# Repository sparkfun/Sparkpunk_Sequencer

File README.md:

SparkPunk Sequencer
===================

[
*SparkPunk Sequencer(KIT-12707)*](https://www.sparkfun.com/products/12707)

The SparkPunk Sequencer is a musical control voltage sequencer designed to control the 
[SparkPunk Sound Generator](https://www.sparkfun.com/products/11177). 
With the pair, you can create ten-step musical motifs, but there are hidden opportunities in the sequencer: 
it can be modified and connected to external hardware in clever and interesting ways. 

Board comes as a soldering kit. 

Repository Contents
-------------------
* **/Hardware** - All Eagle design files (.brd, .sch, .STL)
* **/Sims** - LTSpice files

License Information
-------------------
The hardware is released under [Creative Commons ShareAlike 4.0 International](https://creativecommons.org/licenses/by-sa/4.0/).

Distributed as-is; no warranty is given.

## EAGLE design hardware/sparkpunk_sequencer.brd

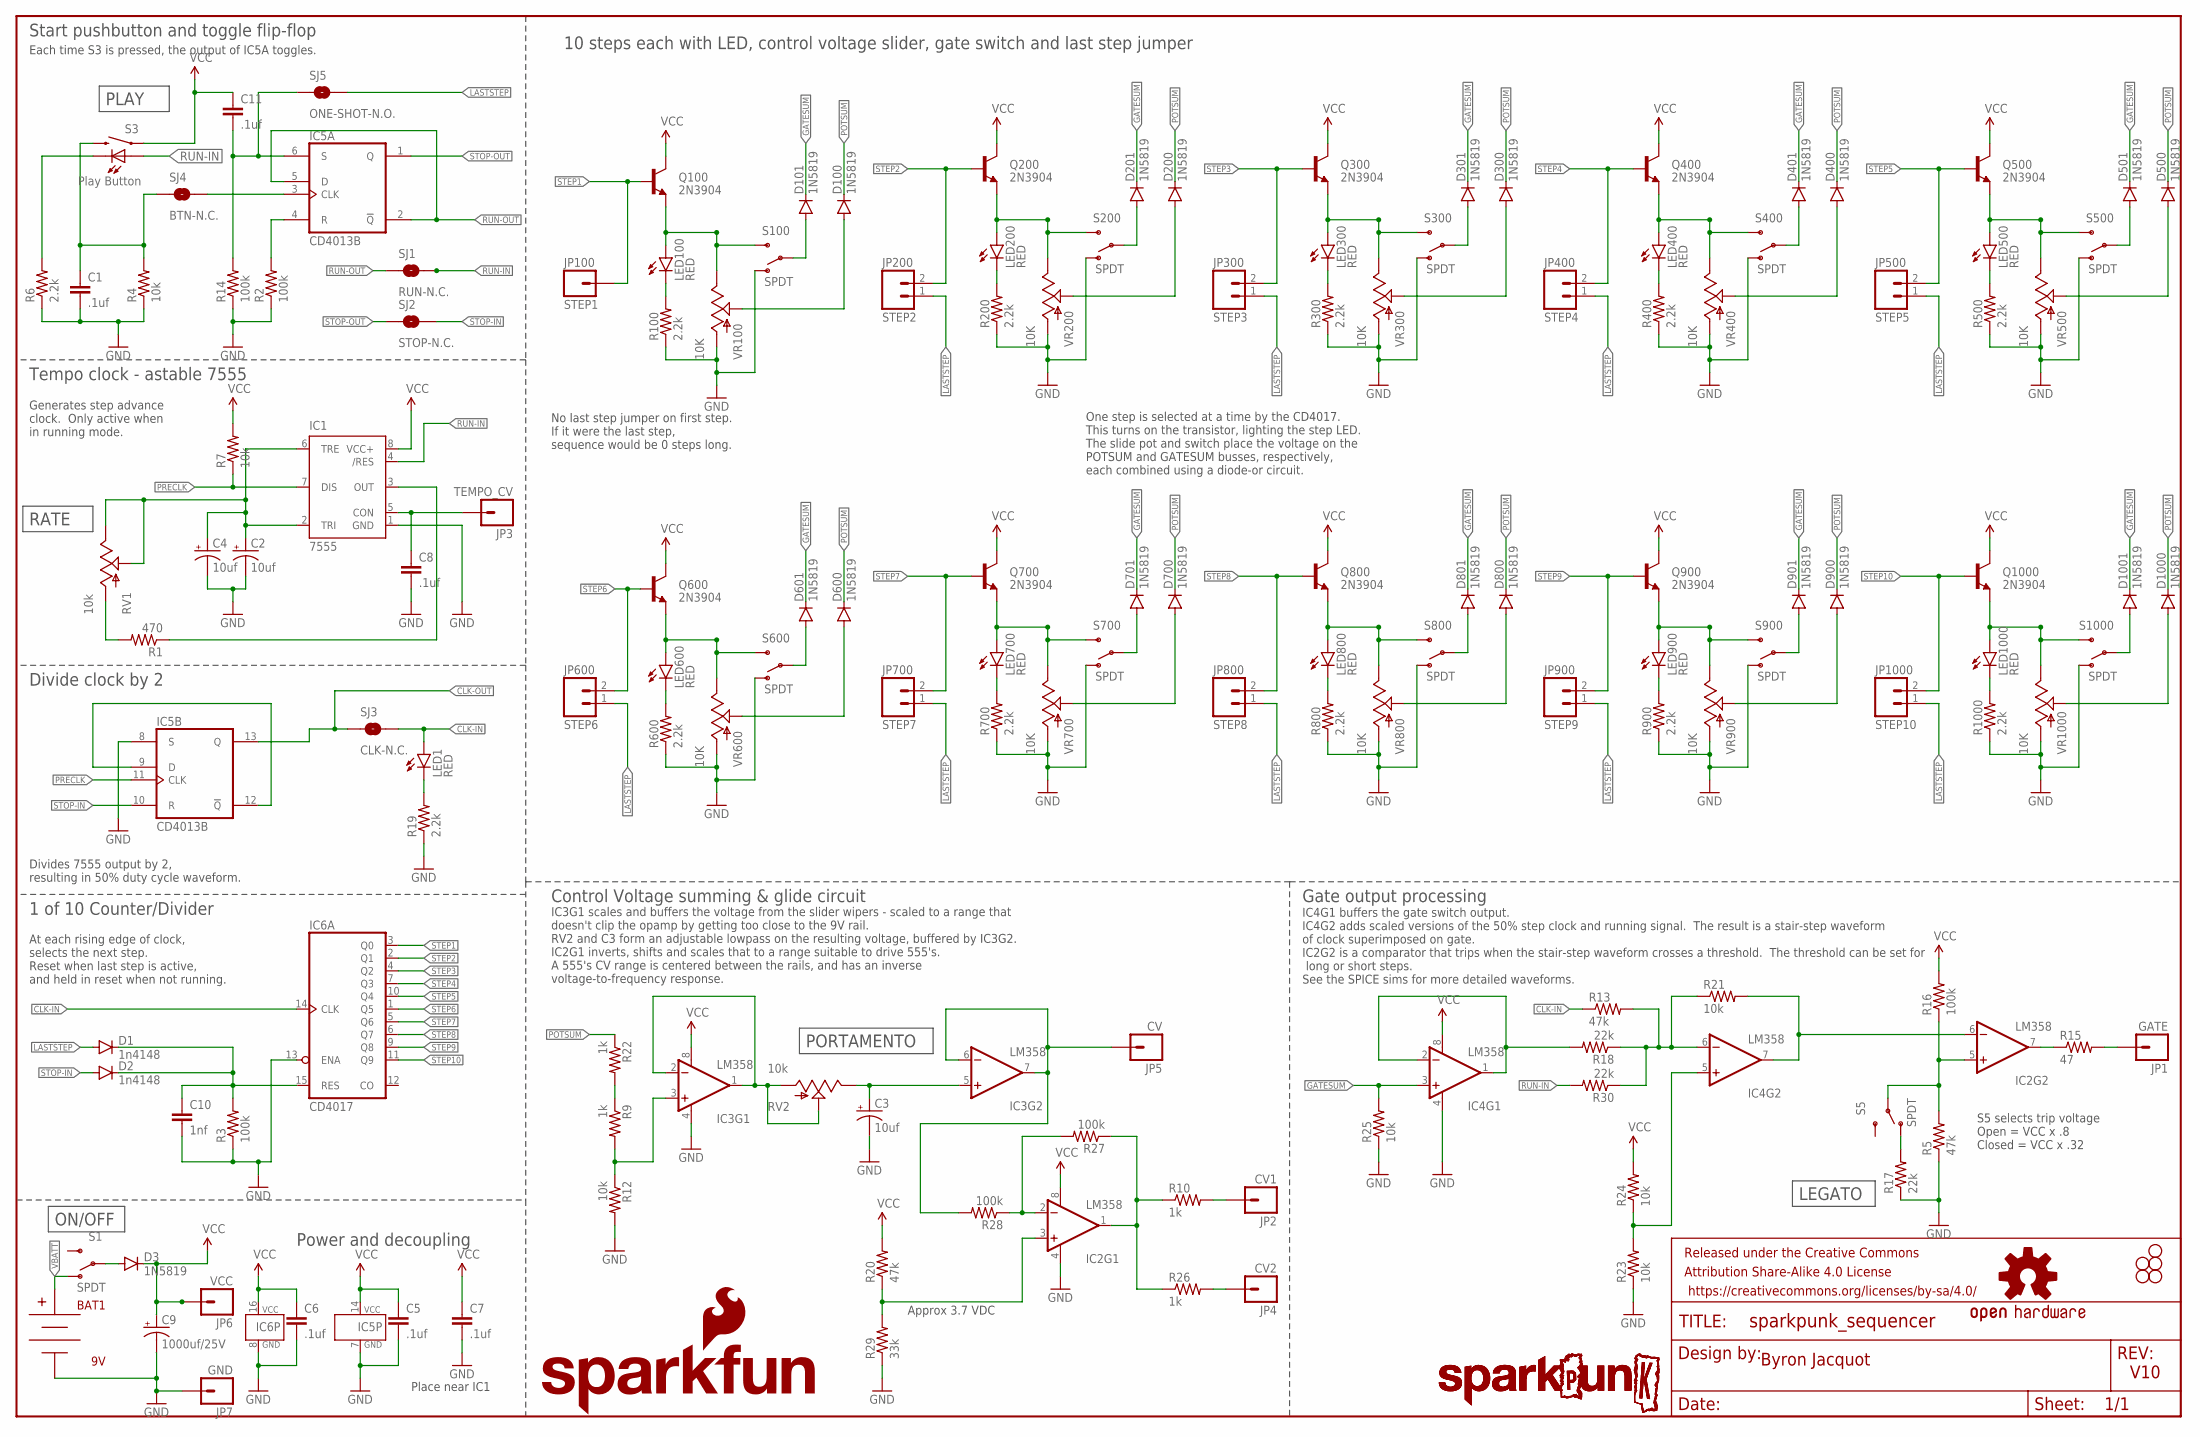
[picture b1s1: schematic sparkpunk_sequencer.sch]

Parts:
BAT1: 9V; BC9VPC_KIT
C1, C5, C6, C7, C8, C11: .1uf; CAP-PTH-SMALL-KIT
C2, C3, C4: 10uf; CPOL-RADIAL-10UF-25V-KIT
C9: 1000uf/25V; CPOL-RADIAL-1000UF-25V-KIT
C10: 1nf; CAP-PTH-SMALL-KIT
D1, D2: 1n4148; DIODE-1N4148-KIT
D3, D100, D101, D200, D201, D300, D301, D400, D401, D500, D501, D600, D601, D700, D701, D800, D801, D900, D901, D1000, D1001: 1N5819; DIODE-1N4001-KIT
FRAME1: FRAME-LEDGER; CREATIVE_COMMONS
IC1: 7555; DIP08-KIT
IC2, IC3, IC4: LM358; DIP08-KIT
IC5: CD4013B; DIL14-KIT
IC6: CD4017; DIL16-KIT
JP1: GATE; 1X01NS
JP2: CV1; 1X01NS
JP3: TEMPO_CV; 1X01NS
JP4: CV2; 1X01NS
JP5: CV; 1X01NS
JP6: VCC; 1X01NS
JP7: GND; 1X01NS
JP100: STEP1; 1X01NS
JP200: STEP2; 1X02_NO_SILK
JP300: STEP3; 1X02_NO_SILK
JP400: STEP4; 1X02_NO_SILK
JP500: STEP5; 1X02_NO_SILK
JP600: STEP6; 1X02_NO_SILK
JP700: STEP7; 1X02_NO_SILK
JP800: STEP8; 1X02_NO_SILK
JP900: STEP9; 1X02_NO_SILK
JP1000: STEP10; 1X02_NO_SILK
LED1, LED100, LED200, LED300, LED400, LED500, LED600, LED700, LED800, LED900, LED1000: RED; LED5MM-KIT
LOGO1: SPARKPUNK_LOGO.2_INCH_TALL; SPARKPUNK_LOGO_.2
LOGO2: OSHW-LOGOM; OSHW-LOGO-M
LOGO3: SPARKPUNK_LOGO.1INCH_TALL; SPARKPUNK_LOGO_.1
LOGO4: SFE_LOGO_NAME_FLAME.4_INCH; SFE_LOGO_NAME_FLAME_.4
Q100, Q200, Q300, Q400, Q500, Q600, Q700, Q800, Q900, Q1000: 2N3904; TO-92-AMMO
R1: 470; AXIAL-0.3EZ
R2, R3, R14, R16, R27, R28: 100k; AXIAL-0.3EZ
R4, R7, R12, R21, R23, R24, R25: 10k; AXIAL-0.3EZ
R5, R13, R20: 47k; AXIAL-0.3EZ
R6, R19, R100, R200, R300, R400, R500, R600, R700, R800, R900, R1000: 2.2k; AXIAL-0.3EZ
R9, R10, R22, R26: 1k; AXIAL-0.3EZ
R15: 47; AXIAL-0.3EZ
R17, R18, R30: 22k; AXIAL-0.3EZ
R29: 33k; AXIAL-0.3EZ
RV1, RV2: 10k; ALPS_POT_KIT
S1, S5, S100, S200, S300, S400, S500, S600, S700, S800, S900, S1000: SPDT; SWITCH-SPDT_KIT
S3: Play Button; TACTILE-PTH-LED-12MM-EZ
SJ1: RUN-N.C.; SJ_2S-TRACE-PTH
SJ2: STOP-N.C.; SJ_2S-TRACE-PTH
SJ3: CLK-N.C.; SJ_2S-TRACE-PTH
SJ4: BTN-N.C.; SJ_2S-TRACE-PTH
SJ5: ONE-SHOT-N.O.; SJ_2S-PTH
STANDOFF1, STANDOFF2, STANDOFF3, STANDOFF5, STANDOFF6: STAND-OFF
VR100, VR200, VR300, VR400, VR500, VR600, VR700, VR800, VR900, VR1000: 10K; SLIDER-MEDIUM-KIT

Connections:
555OUT: IC1.3 (OUT), R1.P$1 (1)
BTN-OUT: C1.1, R4.P$2 (2), S3.2, SJ4.1
CLK-IN: IC6.14 (CLK), LED1.A, R13.P$1 (1), SJ3.2
CLK-OUT: IC5.13 (Q), SJ3.1
GATESUM: D101.C, D201.C, D301.C, D401.C, D501.C, D601.C, D701.C, D801.C, D901.C, D1001.C, IC4.3 (+IN), R25.P$2 (2)
GND: BAT1.V-, C1.2, C2.2 (-), C3.2 (-), C4.2 (-), C5.2, C6.2, C7.2, C8.2, C9.-, C10.2, IC1.1 (GND), IC2.4 (V-), IC3.4 (V-), IC4.4 (V-), IC5.7 (GND), IC5.8 (S), IC6.8 (GND), IC6.13 (ENA), JP7.1, R2.P$1 (1), R3.P$1 (1), R4.P$1 (1), R5.P$1 (1), R6.P$1 (1), R12.P$2 (2), R14.P$1 (1), R17.P$1 (1), R19.P$1 (1), R23.P$1 (1), R25.P$1 (1), R29.P$1 (1), R100.P$1 (1), R200.P$1 (1), R300.P$1 (1), R400.P$1 (1), R500.P$1 (1), R600.P$1 (1), R700.P$1 (1), R800.P$1 (1), R900.P$1 (1), R1000.P$1 (1), S100.1 (O), S200.1 (O), S300.1 (O), S400.1 (O), S500.1 (O), S600.1 (O), S700.1 (O), S800.1 (O), S900.1 (O), S1000.1 (O), VR100.BOTTOM (A), VR200.BOTTOM (A), VR300.BOTTOM (A), VR400.BOTTOM (A), VR500.BOTTOM (A), VR600.BOTTOM (A), VR700.BOTTOM (A), VR800.BOTTOM (A), VR900.BOTTOM (A), VR1000.BOTTOM (A)
LASTSTEP: D1.A, JP200.1, JP300.1, JP400.1, JP500.1, JP600.1, JP700.1, JP800.1, JP900.1, JP1000.1, SJ5.2
unnamed: LED100.A, Q100.1 (E), S100.3 (S), VR100.TOP (E)
unnamed: LED100.K (C), R100.P$2 (2)
unnamed: D101.A, S100.2
unnamed: D100.A, VR100.WIPER (S)
unnamed: R1.P$2 (2), RV1.P$3 (A)
unnamed: IC3.1 (OUT), IC3.2 (-IN), RV2.P$2 (S), RV2.P$3 (A)
unnamed: C8.1, IC1.5 (CON), JP3.1
unnamed: R6.P$2 (2), S3.C
unnamed: IC5.4 (R), R2.P$2 (2)
unnamed: C2.1 (+), C4.1 (+), IC1.2 (TRI), IC1.6 (TRE), RV1.P$1 (E), RV1.P$2 (S)
unnamed: IC4.1 (OUT), IC4.2 (-IN), R18.P$2 (2)
unnamed: LED1.K (C), R19.P$2 (2)
unnamed: C10.1, D1.C, D2.C, IC6.15 (RES), R3.P$2 (2)
unnamed: IC3.3 (+IN), R9.P$2 (2), R12.P$1 (1)
unnamed: R9.P$1 (1), R22.P$2 (2)
unnamed: IC2.2 (-IN), R27.P$2 (2), R28.P$1 (1)
unnamed: C3.1 (+), IC3.5 (+IN), RV2.P$1 (E)
unnamed: IC2.3 (+IN), R20.P$1 (1), R29.P$2 (2)
unnamed: JP1.1, R15.P$2 (2)
unnamed: IC5.3 (CLK), SJ4.2
unnamed: IC2.5 (+IN), R5.P$2 (2), R16.P$1 (1), S5.2
unnamed: IC2.7 (OUT), R15.P$1 (1)
unnamed: R17.P$2 (2), S5.1 (O)
unnamed: IC5.9 (D), IC5.12 (!Q)
unnamed: LED200.A, Q200.1 (E), S200.3 (S), VR200.TOP (E)
unnamed: LED200.K (C), R200.P$2 (2)
unnamed: D200.A, VR200.WIPER (S)
unnamed: D201.A, S200.2
unnamed: LED300.A, Q300.1 (E), S300.3 (S), VR300.TOP (E)
unnamed: LED300.K (C), R300.P$2 (2)
unnamed: D300.A, VR300.WIPER (S)
unnamed: D301.A, S300.2
unnamed: LED400.A, Q400.1 (E), S400.3 (S), VR400.TOP (E)
unnamed: LED400.K (C), R400.P$2 (2)
unnamed: D400.A, VR400.WIPER (S)
unnamed: D401.A, S400.2
unnamed: LED500.A, Q500.1 (E), S500.3 (S), VR500.TOP (E)
unnamed: LED500.K (C), R500.P$2 (2)
unnamed: D500.A, VR500.WIPER (S)
unnamed: D501.A, S500.2
unnamed: LED600.A, Q600.1 (E), S600.3 (S), VR600.TOP (E)
unnamed: LED600.K (C), R600.P$2 (2)
unnamed: D600.A, VR600.WIPER (S)
unnamed: D601.A, S600.2
unnamed: LED700.A, Q700.1 (E), S700.3 (S), VR700.TOP (E)
unnamed: LED700.K (C), R700.P$2 (2)
unnamed: D700.A, VR700.WIPER (S)
unnamed: D701.A, S700.2
unnamed: LED800.A, Q800.1 (E), S800.3 (S), VR800.TOP (E)
unnamed: LED800.K (C), R800.P$2 (2)
unnamed: D800.A, VR800.WIPER (S)
unnamed: D801.A, S800.2
unnamed: LED900.A, Q900.1 (E), S900.3 (S), VR900.TOP (E)
unnamed: LED900.K (C), R900.P$2 (2)
unnamed: D900.A, VR900.WIPER (S)
unnamed: D901.A, S900.2
unnamed: LED1000.A, Q1000.1 (E), S1000.3 (S), VR1000.TOP (E)
unnamed: LED1000.K (C), R1000.P$2 (2)
unnamed: D1000.A, VR1000.WIPER (S)
unnamed: D1001.A, S1000.2
unnamed: C11.2, IC5.6 (S), R14.P$2 (2), SJ5.1
unnamed: IC4.6 (-IN), R13.P$2 (2), R18.P$1 (1), R21.P$1 (1), R30.P$1 (1)
unnamed: IC3.6 (-IN), IC3.7 (OUT), JP5.1, R28.P$2 (2)
unnamed: IC2.1 (OUT), R10.P$1 (1), R26.P$1 (1), R27.P$1 (1)
unnamed: JP4.1, R26.P$2 (2)
unnamed: JP2.1, R10.P$2 (2)
unnamed: IC2.6 (-IN), IC4.7 (OUT), R21.P$2 (2)
unnamed: IC4.5 (+IN), R23.P$2 (2), R24.P$1 (1)
unnamed: D3.A, S1.2
POTSUM: D100.C, D200.C, D300.C, D400.C, D500.C, D600.C, D700.C, D800.C, D900.C, D1000.C, R22.P$1 (1)
PRECLK: IC1.7 (DIS), IC5.11 (CLK), R7.P$1 (1)
RUN-IN: IC1.4 (/RES), R30.P$2 (2), S3.A, SJ1.2
RUN-OUT: IC5.2 (!Q), IC5.5 (D), SJ1.1
STEP1: IC6.3 (Q0), JP100.1, Q100.2 (B)
STEP2: IC6.2 (Q1), JP200.2, Q200.2 (B)
STEP3: IC6.4 (Q2), JP300.2, Q300.2 (B)
STEP4: IC6.7 (Q3), JP400.2, Q400.2 (B)
STEP5: IC6.10 (Q4), JP500.2, Q500.2 (B)
STEP6: IC6.1 (Q5), JP600.2, Q600.2 (B)
STEP7: IC6.5 (Q6), JP700.2, Q700.2 (B)
STEP8: IC6.6 (Q7), JP800.2, Q800.2 (B)
STEP9: IC6.9 (Q8), JP900.2, Q900.2 (B)
STEP10: IC6.11 (Q9), JP1000.2, Q1000.2 (B)
STOP-IN: D2.A, IC5.10 (R), SJ2.2
STOP-OUT: IC5.1 (Q), SJ2.1
VBATT: BAT1.V+, S1.1 (O)
VCC: C5.1, C6.1, C7.1, C9.+, C11.1, D3.C, IC1.8 (VCC+), IC2.8 (V+), IC3.8 (V+), IC4.8 (V+), IC5.14 (VCC), IC6.16 (VCC), JP6.1, Q100.3 (C), Q200.3 (C), Q300.3 (C), Q400.3 (C), Q500.3 (C), Q600.3 (C), Q700.3 (C), Q800.3 (C), Q900.3 (C), Q1000.3 (C), R7.P$2 (2), R16.P$2 (2), R20.P$2 (2), R24.P$2 (2), S3.4 (1)

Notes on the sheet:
Byron Jacquot
V10
LEGATO
PORTAMENTO
RATE
PLAY
Place near IC1
Power and decoupling
1 of 10 Counter/Divider
Divide clock by 2
Tempo clock - astable 7555
Start pushbutton and toggle flip-flop
Control Voltage summing & glide circuit
Gate output processing
10 steps each with LED, control voltage slider, gate switch and last step jumper
No last step jumper on first step. If it were the last step, sequence would be 0 steps long.
Each time S3 is pressed, the output of IC5A toggles.
Divides 7555 output by 2, resulting in 50% duty cycle waveform.
At each rising edge of clock, selects the next step. Reset when last step is active, and held in reset when not running.
Generates step advance clock. Only active when in running mode.
IC3G1 scales and buffers the voltage from the slider wipers - scaled to a range that doesn't clip the opamp by getting too close to the 9V rail. RV2 and C3 form an adjustable lowpass on the resulting voltage, buffered by IC3G2. IC2G1 inverts, shifts and scales that to a range suitable to drive 555'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
IC4G1 buffers the gate switch output. IC4G2 adds scaled versions of the 50% step clock and running signal. The result is a stair-step waveform of clock superimposed on gate. IC2G2 is a comparator that trips when the stair-step waveform crosses a threshold. The threshold can be set for long or short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
S5 selects trip voltage Open = VCC x .8 Closed = VCC x .32
One step is selected at a time by the CD4017. This turns on the transistor, lighting the step LED. The slide pot and switch place the voltage on the POTSUM and GATESUM busses, respectively, each combined using a diode-or circuit.
Approx 3.7 VDC
ON/OFF

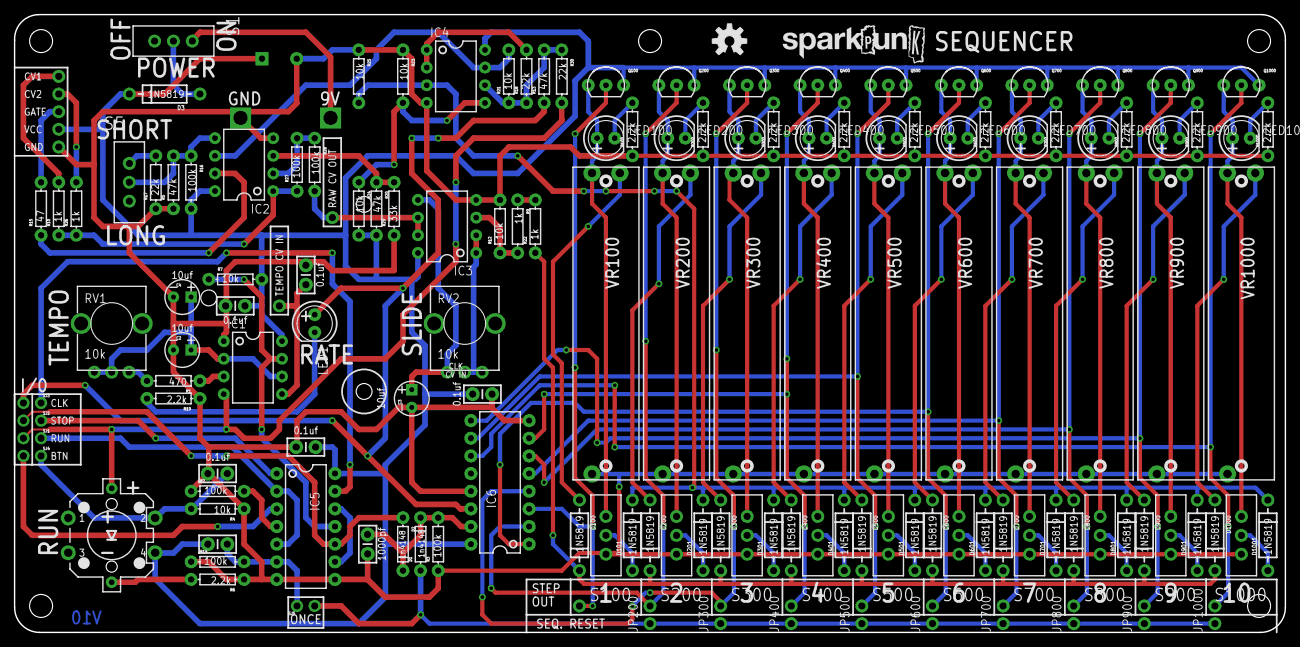
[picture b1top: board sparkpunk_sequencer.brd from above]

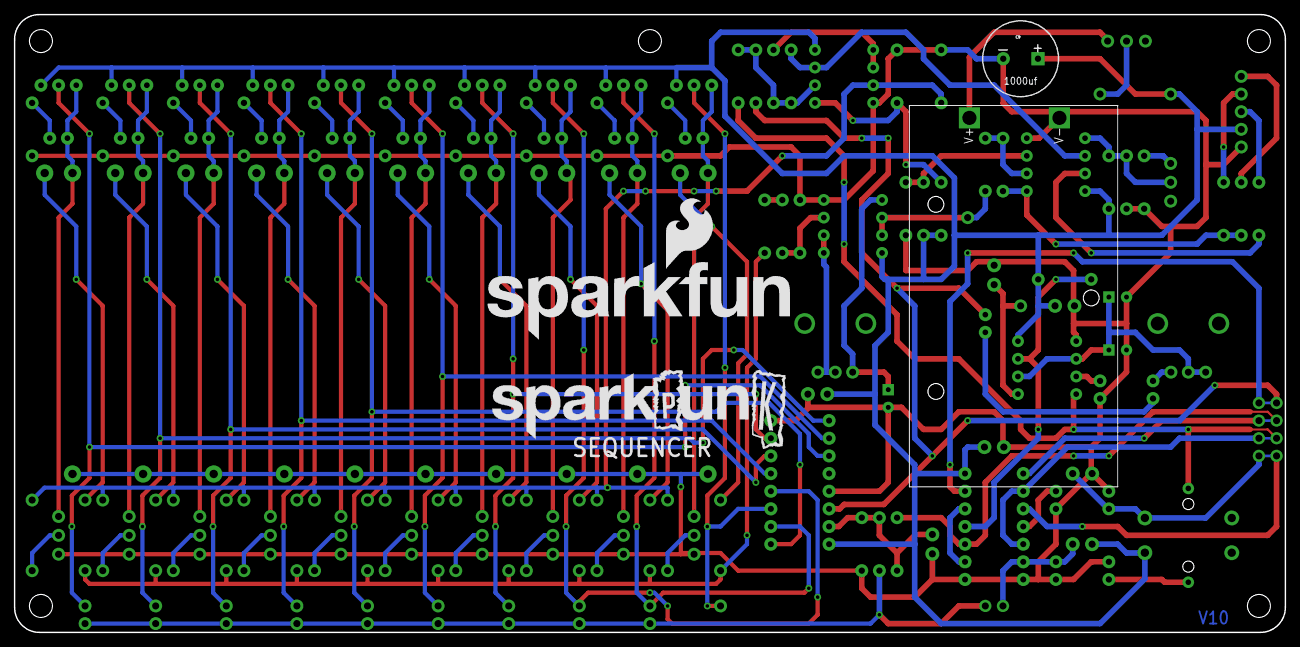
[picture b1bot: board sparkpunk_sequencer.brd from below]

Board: 2 copper layers, 182.9 x 88.9 mm, 157 parts (4 on the bottom side), 94 nets.

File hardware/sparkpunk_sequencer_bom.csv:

Qty	Ref Des	Lib	Pkg	Val	Prod ID	Distributor	Dist. ID	Desc1	Desc2	Cost
1	IC5	SparkFun-DigitalIC	DIL14-KIT	CD4013B	IC-11896			IC CD4013BE (PTH)	IC D-TYPE POS TRG DUAL 14DIP	0.38520
21	D100, D200, D300, D400, D500, D600, D700, D800, D900, D1000, D101, D201, D301, D401, D501, D1001, D901, D801, D601, D701, D3	SparkFun-DiscreteSemi	DIODE-1N4001-KIT	1N5819	DIO-11895			DIODE SCHOTTKY 1N5819 (PTH)	DIODE SCHOTTKY 40V 1A DO41	0.02500
1	FRAME1	SparkFun-Aesthetics	CREATIVE_COMMONS					 	 	 
30	GND1, GND2, GND3, GND4, GND5, GND6, GND7, GND10, GND11, GND12, GND14, GND15, GND16, GND17, GND18, GND19, GND20, GND21, GND22, GND23, GND24, GND8, GND9, GND25, GND26, GND13, GND27, GND28, GND29, GND30	SparkFun-Aesthetics						 	 	 
5	STANDOFF1, STANDOFF2, STANDOFF3, STANDOFF5, STANDOFF6	SparkFun-Electromechanical	STAND-OFF					 	 	 
23	SUPPLY1, SUPPLY2, SUPPLY3, SUPPLY4, SUPPLY5, SUPPLY6, SUPPLY7, SUPPLY8, SUPPLY9, SUPPLY10, SUPPLY11, SUPPLY12, SUPPLY13, SUPPLY14, SUPPLY15, SUPPLY16, SUPPLY17, SUPPLY18, SUPPLY19, SUPPLY20, SUPPLY21, SUPPLY22, SUPPLY23	SparkFun-Aesthetics						 	 	 
1	LOGO3	SparkFun-Aesthetics	SPARKPUNK_LOGO_.1					 	 	 
1	LOGO1	SparkFun-Aesthetics	SPARKPUNK_LOGO_.2					 	 	 
1	LOGO4	SparkFun-Aesthetics	SFE_LOGO_NAME_FLAME_.4	SFE_LOGO_NAME_FLAME.4_INCH				 	 	 
1	JP200	SparkFun-Connectors	1X02_NO_SILK	STEP2				 	 	 
1	JP300	SparkFun-Connectors	1X02_NO_SILK	STEP3				 	 	 
1	JP400	SparkFun-Connectors	1X02_NO_SILK	STEP4				 	 	 
1	JP500	SparkFun-Connectors	1X02_NO_SILK	STEP5				 	 	 
1	JP700	SparkFun-Connectors	1X02_NO_SILK	STEP7				 	 	 
1	JP800	SparkFun-Connectors	1X02_NO_SILK	STEP8				 	 	 
1	JP900	SparkFun-Connectors	1X02_NO_SILK	STEP9				 	 	 
1	JP1000	SparkFun-Connectors	1X02_NO_SILK	STEP10				 	 	 
1	JP600	SparkFun-Connectors	1X02_NO_SILK	STEP6				 	 	 
10	VR100, VR200, VR300, VR400, VR500, VR600, VR700, VR800, VR900, VR1000	SparkFun-Electromechanical	SLIDER-MEDIUM-KIT	10K	RES-11931			Slide Pot - Medium (10k Linear Taper) (PTH)	  	0.15000
11	LED100, LED200, LED300, LED400, LED500, LED600, LED700, LED800, LED900, LED1000, LED1	SparkFun-LED	LED5MM-KIT	RED	DIO-09529			Basic LED -  5mm Red (PTH)	  	0.01903
2	RV1, RV2	SparkFun-Electromechanical	ALPS_POT_KIT	10k	RES-09177			Trimpot Tall 10k (PTH)	POT 10K OHM 9MM VERT NO BUSHING Square - 0.453	0.07920
12	R100, R6, R200, R300, R400, R500, R600, R700, R800, R900, R1000, R19	SparkFun-Resistors	AXIAL-0.3EZ	2.2k	RES-10691			Resistor 2.2k Ohm - 1/4W - 5% (PTH)	  	0.02880
6	R2, R16, R3, R14, R27, R28	SparkFun-Resistors	AXIAL-0.3EZ	100k	RES-10686			Resistor 100k Ohm - 1/4W - 5% (PTH)	  	0.02880
7	R4, R7, R21, R23, R24, R25, R12	SparkFun-Resistors	AXIAL-0.3EZ	10k	RES-09435			Resistor 10k Ohm - 1/4W  5% (PTH)	  	0.00523
3	R13, R20, R5	SparkFun-Resistors	AXIAL-0.3EZ	47k	RES-10687			Resistor 47k Ohm - 1/4W - 5% (PTH)	  	0.02880
1	R15	SparkFun-Resistors	AXIAL-0.3EZ	47	RES-10697			Resistor 47 Ohm - 1/4W - 5% (PTH)	  	0.02880
3	R17, R18, R30	SparkFun-Resistors	AXIAL-0.3EZ	22k	RES-10688			Resistor 22k Ohm - 1/4W - 5% (PTH)	used in strips of 25 for resistor kit	0.00000
1	R1	SparkFun-Resistors	AXIAL-0.3EZ	470	RES-10693			Resistor 470 Ohm - 1/4W - 5% (PTH)	used in strips of 25 for resistor kit	0.00495
4	R22, R9, R10, R26	SparkFun-Resistors	AXIAL-0.3EZ	1k	RES-09435			Resistor 10k Ohm - 1/4W  5% (PTH)	  	0.00523
1	R29	SparkFun-Resistors	AXIAL-0.3EZ	33k	RES-10687			Resistor 47k Ohm - 1/4W - 5% (PTH)	  	0.02880
1	S3	SparkFun-Electromechanical	TACTILE-PTH-LED-12MM-EZ	Play Button	SWCH-11758			LED Tactile Button - Red (PTH)	  	0.48000
4	C2, C3, C4, C9	SparkFun-Capacitors	CPOL-RADIAL-10UF-25V-KIT	10uf	CAP-08440			Cap 10uF - 25V - 20% (PTH)	0.197	0.03033
1	C10	SparkFun-Capacitors	CAP-PTH-SMALL-KIT	1nf	CAP-09182			Cap 1nF - 100V - 5% (PTH)	  	0.08100
1	IC6	SparkFun-DigitalIC	DIL16-KIT	CD4017		Digikey	296-2037-5-ND	 	 	 
2	D1, D2	SparkFun-DiscreteSemi	DIODE-1N4148-KIT	1n4148	DIO-08378			Diode 1N4148 (PTH)	DIODE SW HS 100V 200MA DO-35	0.00743
3	IC3, IC4, IC2	SparkFun-AnalogIC	DIP08-KIT	LM358	IC-09172			IC LM358 (PTH)	IC OP AMP LOW PWR DUAL 8-DIP	0.13500
1	IC1	SparkFun-AnalogIC	DIP08-KIT	7555		digikey	ICM7555IPAZ-ND	 	 	 
12	S100, S5, S200, S300, S400, S500, S600, S700, S800, S900, S1000, S1	SparkFun-Electromechanical	SWITCH-SPDT_KIT	SPDT	SWCH-08261			Mini Power Switch - Black (PTH)	  	0.12938
5	C1, C5, C6, C7, C8	SparkFun-Capacitors	CAP-PTH-SMALL-KIT	.1uf	CAP-08370			Cap 0.1uF - 50V - 20% (PTH)	  	0.04300
1	BAT1	SparkFun-Connectors	BC9VPC_KIT	9V				 	 	 
1	LOGO2	SparkFun-Aesthetics	OSHW-LOGO-M					 	 	 
1	SJ5	SparkFun-Passives	SJ_2S-PTH	ONE-SHOT-N.O.				 	 	 
1	JP1	SparkFun-Connectors	1X01NS	GATE				 	 	 
1	JP2	SparkFun-Connectors	1X01NS	CV1				 	 	 
1	JP100	SparkFun-Connectors	1X01NS	STEP1				 	 	 
1	JP3	SparkFun-Connectors	1X01NS	TEMPO_CV				 	 	 
1	JP4	SparkFun-Connectors	1X01NS	CV2				 	 	 
1	JP5	SparkFun-Connectors	1X01NS	CV				 	 	 
1	JP6	SparkFun-Connectors	1X01NS	VCC				 	 	 
1	JP7	SparkFun-Connectors	1X01NS	GND				 	 	 
10	Q100, Q200, Q300, Q400, Q500, Q600, Q700, Q800, Q900, Q1000	SparkFun-DiscreteSemi	TO-92-AMMO	2N3904	TRANS-08447			Transistor NPN 2N3904 (PTH)	2N Series 40 V 200 mA Through Hole NPN Silicon General Purpose Transistor TO-92	0.01680
1	SJ1	SparkFun-Passives	SJ_2S-TRACE-PTH	RUN-N.C.				 	 	 
1	SJ2	SparkFun-Passives	SJ_2S-TRACE-PTH	STOP-N.C.				 	 	 
1	SJ3	SparkFun-Passives	SJ_2S-TRACE-PTH	CLK-N.C.				 	 	 
1	SJ4	SparkFun-Passives	SJ_2S-TRACE-PTH	BTN-N.C.

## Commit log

2014-01-03 Initial checkin
2014-01-07 PCB updates after review
2014-01-08 Small updates after creating BOM
2014-04-25 Ready for second proto
    Lots of tweaking on the output stages and other details, based on
    prototype evaluation.
2014-04-25 Ready for second prototype
    Many changes based on prototype evaluation.
2014-04-25 Removing BOM
2014-04-26 After library updates
    Picking up PROD_ID's for a few parts that didn't have them before.
    No changes to the layout.
2014-06-13 Adding *.log to gitignore
2014-06-23 Ready for red review
    Incorporating all changes from second round of protos, builder feedback,
    etc.
2014-08-19 Updating for release
    Mainly bringing SPICE files to match final implementation, small
    notation change on Eagle schematic
2014-08-21 Adding product info to README
2014-08-21 Removing blank lines for demo
2014-08-21 Adding prodact image to README

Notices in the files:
parts and their libraries:
SparkFun-Aesthetics: Licensing: CC v3.0 Share-Alike You are welcome to use this library for commercial purposes.
SparkFun-Aesthetics: Released under the Creative Commons Attribution Share-Alike 4.0 License
SparkFun-Aesthetics: Released under the Creative Commons
